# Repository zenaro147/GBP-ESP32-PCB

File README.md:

# Gameboy Printer Emulator - ESP32 PCB

A simple PCB design using EasyEDA to work with this projects by me:
* [NeoGB Printer](https://github.com/zenaro147/NeoGB-Printer)
* [WiFi GBP Emulator - ESP32 Version](https://github.com/zenaro147/wifi-gbp-emulator/tree/feature/v3-esp32)

## BOM list 
| Component | Where to buy |
| --- | --- |
| ESP32 Dev Board (38 pins) | [AliExpress](https://a.aliexpress.com/_mKXR5OW) |
| OLED Display 128x32 (0.91 inch) (optional) | [AliExpress](https://a.aliexpress.com/_mOHbftG) |
| SD Card/MicroSD Card Module (Choose only one! I recommend the Standard SD module) | [AliExpress - SD Card](https://a.aliexpress.com/_mMWz2km) / [AliExpress - MicroSD](https://a.aliexpress.com/_m0SS4P4) |
| 4 channel Logical Level Shifter (highly recommended) | [AliExpress](https://a.aliexpress.com/_m07pFpU) |
| Female Pin Header with 40 pins (you need at least 38 pins, or 2 with 20pins) | [AliExpress](https://www.aliexpress.com/item/4000096276148.html) |
| PushButton 4.5x4.5mm (any height) - ONLY REV. 1  | [AliExpress](https://www.aliexpress.com/item/1005001629344310.html) |
| PushButton 6x6mm (any height) - ONLY REV. 2 (still W.I.P.) | [AliExpress](https://www.aliexpress.com/item/1005003251295065.html) |
| 5k or 10k resistor | [AliExpress](https://www.aliexpress.com/item/4001082088353.html) |
| MicroUSB Female (optional, but mandatory if you want the charging module)| [AliExpress](https://www.aliexpress.com/item/4000385426649.html) |
| Charging Module with StepUp (5V) - DD05CVSA (optional) | [AliExpress](https://www.aliexpress.com/item/33034500618.html) |
| Micro Switch - SS-12D00G3 (optional, but mandatory if you want the charging module) | [AliExpress](https://www.aliexpress.com/item/1005003938856402.html) |
| 1500mah Li-Po Battery (optional, but mandatory if you want the charging module) | [AliExpress](https://www.aliexpress.com/item/1005003235425542.html) |
| AGB Link Port Connector (optional) | [AliExpress](https://www.aliexpress.com/item/32858521427.html) |
| RGB LED 5mm (optional) | [AliExpress](https://www.aliexpress.com/item/1005002535018824.html) |
| 220R resistor (if you want the LED) | [AliExpress](https://www.aliexpress.com/item/4001082088353.html) |

## How to build
* First of all, solder the resistors, RGB led, button, the level shifter, USB port, and the female pin bar (oh, and the AGB link port, if you have one)
* Put a little bit of in the RGB led jumper to bridge the middle pad to one of the other pads. (If you want a passthrough USB power, make bridge pads too)
* Cut all remaining legs
* Solder the SD/Micro SD module
* Cut all remaining legs
* Solder the male pin head for the charging module (but don't solder the module yet)
* Cut all remaining legs
* Solder the display and the battery
* Cut all remaining legs
* Solder the charging module into the pins

I highly recommend to add some tape to prevent any unwanted contact between the modules (on SD/MicroSD, charging module and display to be more specific) and the solder points

## Inspirations/References
* [Game Boy -related custom hardware by gekkio](https://github.com/Gekkio/gb-hardware)
* [Game Boy WiFi Printer - D1 Mini Shield](https://github.com/cristofercruz/gbp-esp-shield-pcb)
* [Gameboy Link Cable Breakout PCB](https://github.com/Palmr/gb-link-cable)

## External References
* [ESP32-DEVKITC-32D](https://www.snapeda.com/parts/ESP32-DEVKITC-32D/Espressif%20Systems/view-part/)
* [ESP32 Pinout](https://4.bp.blogspot.com/-nGLtB2nUrDg/Wp6DQbzcJMI/AAAAAAAABq0/A6Z46p0SQSEdERWocWL94oUmeATMQre4wCLcBGAs/s1600/3.png)
* [ESP32 dev kit power options](https://techexplorations.com/guides/esp32/begin/power/)
* [Power Supply for ESP32 with Battery Charger & Boost Converter](https://how2electronics.com/power-supply-for-esp32-with-boost-converter-battery-charger/#37V_to_5V_Step-Up_Boost_Converter_Module)
* [ESP32 – Getting Battery charging level](https://www.pangodream.es/esp32-getting-battery-charging-level)

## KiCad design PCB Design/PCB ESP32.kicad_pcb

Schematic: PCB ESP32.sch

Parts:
D1: StatusLED; LED_D5.0mm
D2: PowerLED; LED_D5.0mm
J3: GameBoy_LinkPort; GameBoy_LinkPort_MGB_Horizontal
J4: 5vBatteryPins; PinHeader_1x02_P2.54mm_Horizontal
J5: HV_pins; PinSocket_1x06_P2.54mm_Vertical
J6: LV_pins; PinSocket_1x06_P2.54mm_Vertical
R1, R2: 1k Resistor; R_Axial_DIN0207_L6.3mm_D2.5mm_P10.16mm_Horizontal
R3, R4: 10k Resistor; R_Axial_DIN0207_L6.3mm_D2.5mm_P10.16mm_Horizontal
R5: 4.7k Resistor; R_Axial_DIN0207_L6.3mm_D2.5mm_P10.16mm_Horizontal
SW1: SW_Push; SW_Tactile_Straight_KSA0Axx1LFTR
U1: ESP32_DEVBOARD_WROOM; MODULE_ESP32-DEVKITC-32D
U2: SD_Card_module; PinHeader_1x08_P2.54mm_Vertical
U3: OledDisplay_SSD1305_128_32; PinHeader_1x04_P2.54mm_Vertical
U4: MicroSD_Card_module; PinHeader_1x06_P2.54mm_Vertical

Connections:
GND: D1.1 (K), D2.1 (K), J3.6 (GND), J3.SH, J4.1, J5.4, J6.4, R3.1, R4.2, U1.14, U1.20, U1.26, U2.1, U2.8, U3.4, U4.6
unnamed: D1.2 (A), R1.1
unnamed: D2.2 (A), R2.1
unnamed: J3.1 (VDD), R5.1
unnamed: J3.2 (SO), J5.6
unnamed: J3.3 (SI), J5.5
unnamed: J3.5 (SC), J5.2
unnamed: J4.2, J5.3, R2.2, U1.19, U2.6, U3.3, U4.5
unnamed: J6.2, U1.28
unnamed: J6.3, SW1.2, U1.1
unnamed: J6.5, U1.21
unnamed: J6.6, U1.27
unnamed: R1.2, U1.32
unnamed: R3.2, SW1.1, U1.5
unnamed: R4.1, R5.2, U1.7
unnamed: U1.10, U2.2, U4.4
unnamed: U1.12, U2.3, U4.2
unnamed: U1.15, U2.4, U4.3
unnamed: U1.22, U1.30, U3.2
unnamed: U1.25, U1.31, U3.1
unnamed: U1.35, U2.5, U4.1

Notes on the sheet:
GB Printer Emulator - ESP32 Version
Works to these projects: Wifi GBP Emulator - ESP32 Version (https://bit.ly/3mIIKRQ) BitBoy Clone (https://bit.ly/3zsWsfd)

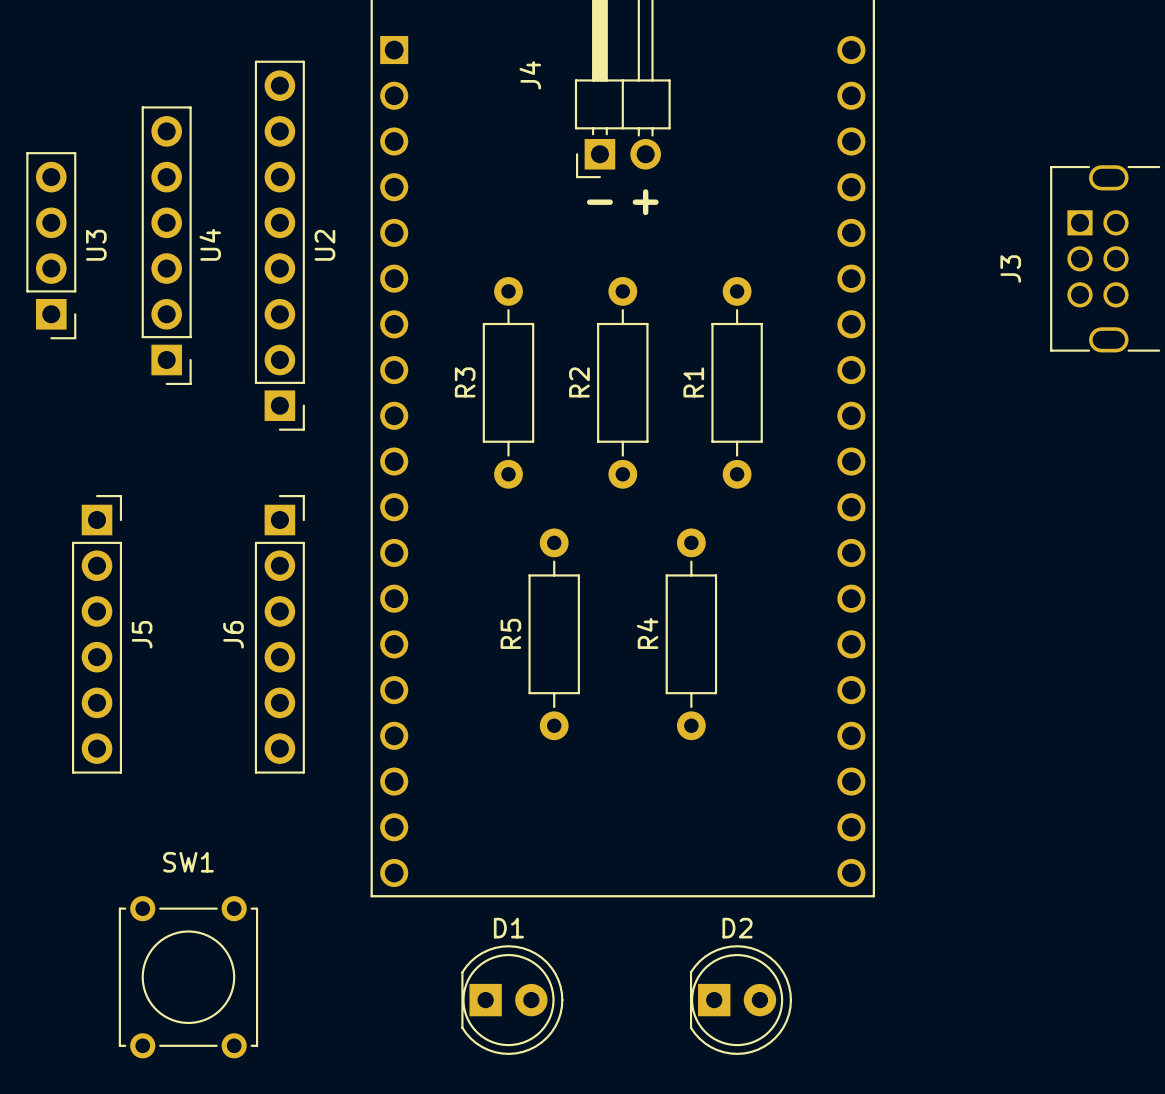
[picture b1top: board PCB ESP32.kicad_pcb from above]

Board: 2 copper layers, 16 parts (0 on the bottom side), 21 nets, no tracks yet.

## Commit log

2021-09-12 Added 3d model case
2022-03-15 Change to EasyEDA
2022-03-15 Remove Files
2022-03-16 Update Files
2022-03-16 Added Copper Area to GND
2022-03-17 Updated Files
2022-04-20 Board Review after first build
2022-04-25 Added some jumpers to avoid the Level Shifter
